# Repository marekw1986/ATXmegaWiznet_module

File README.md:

# ATXmegaWiznet_module

Flash
avrdude -p x128a3u -c avrispmkII -P usb -U flash:w:code.debug.elf

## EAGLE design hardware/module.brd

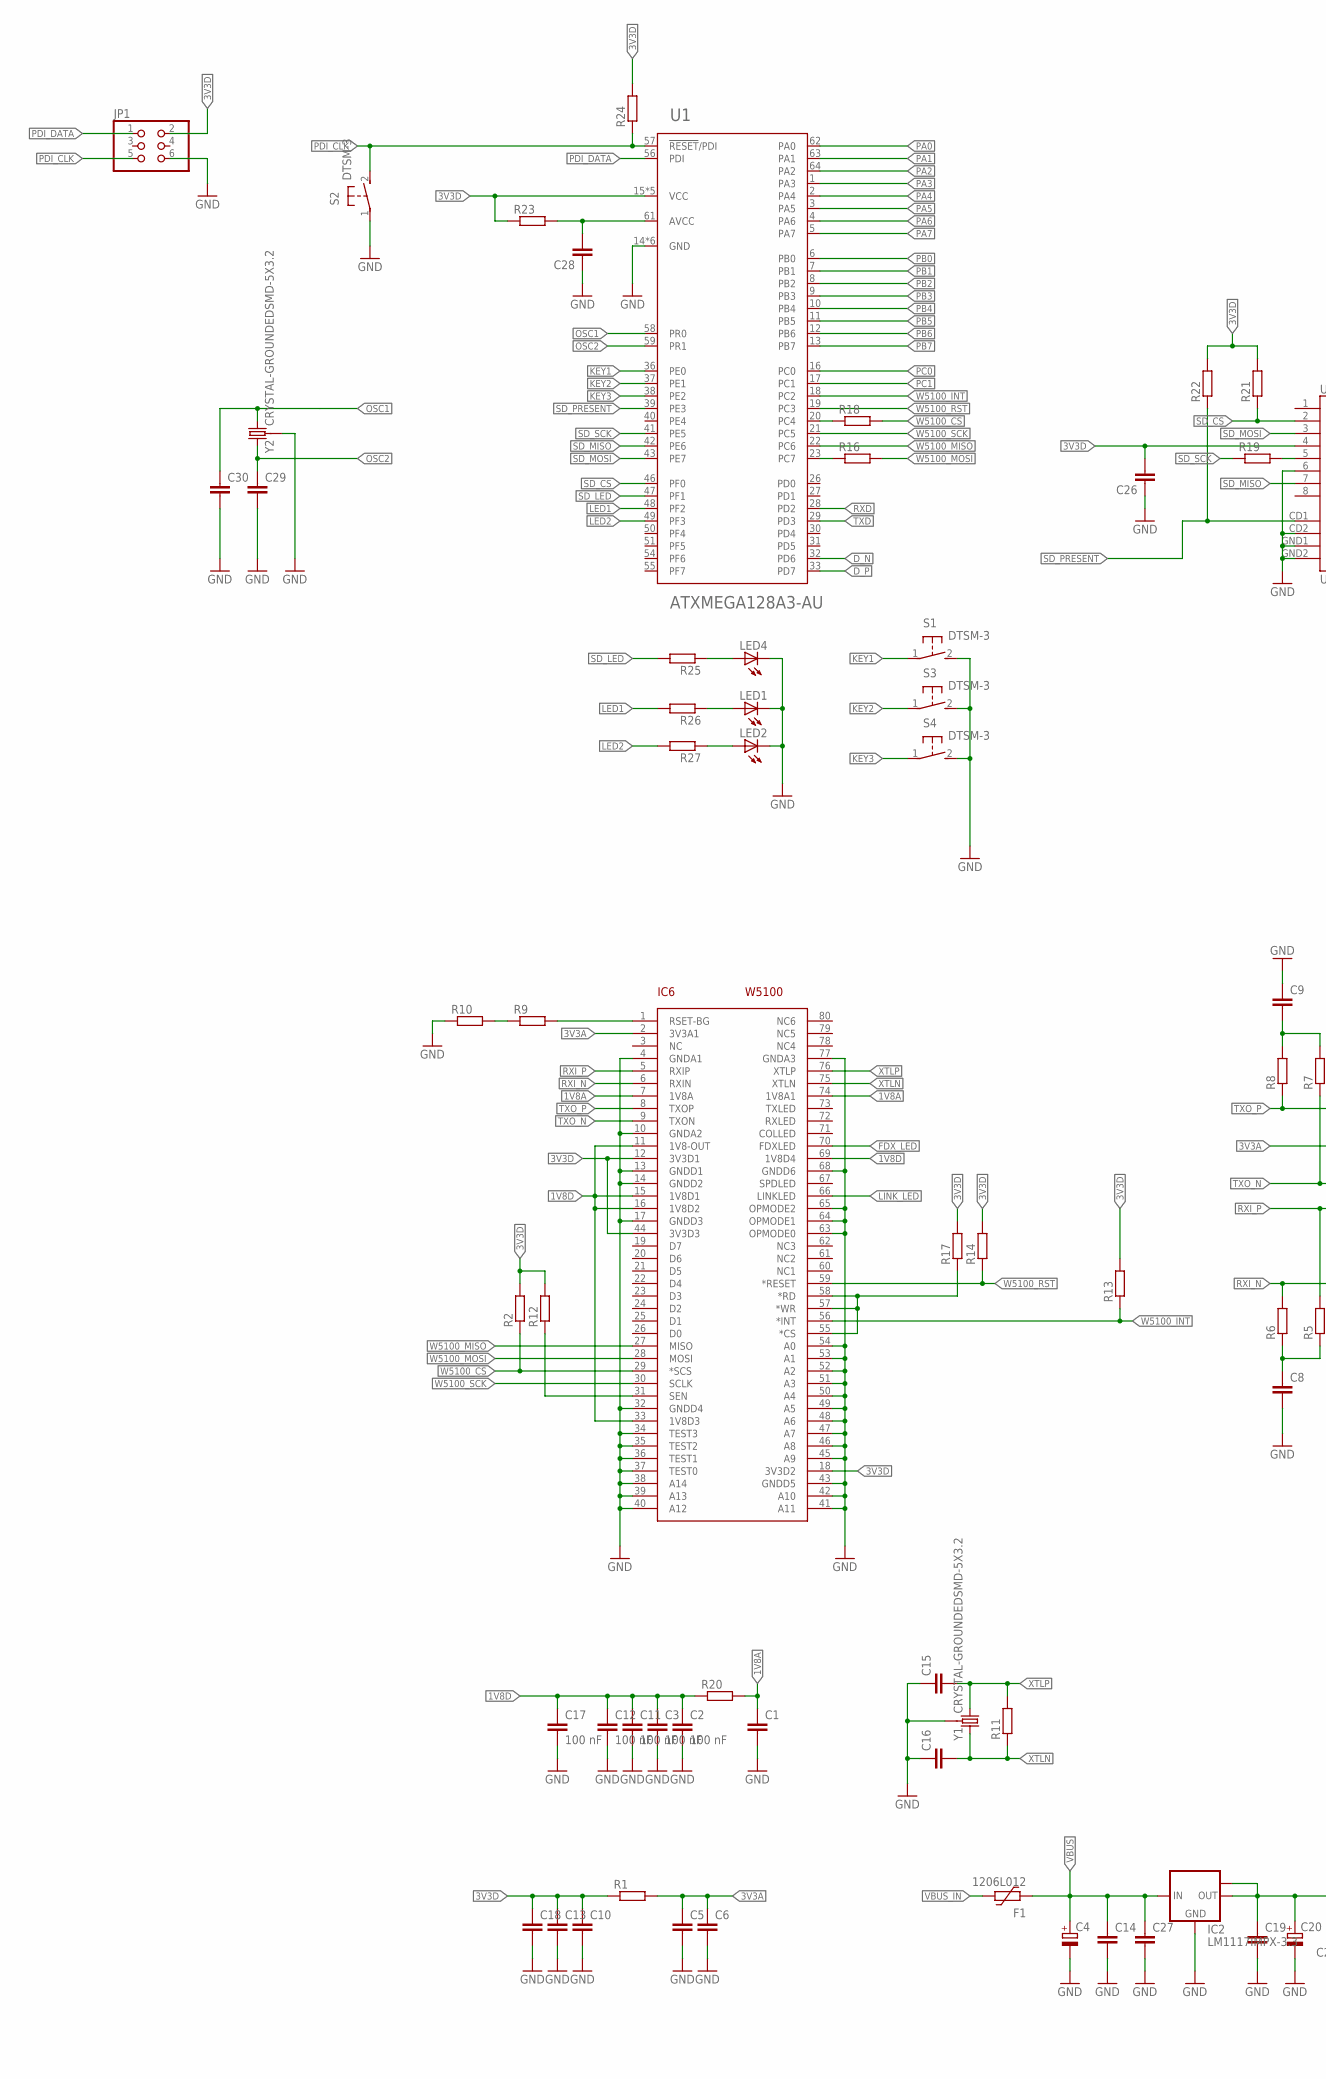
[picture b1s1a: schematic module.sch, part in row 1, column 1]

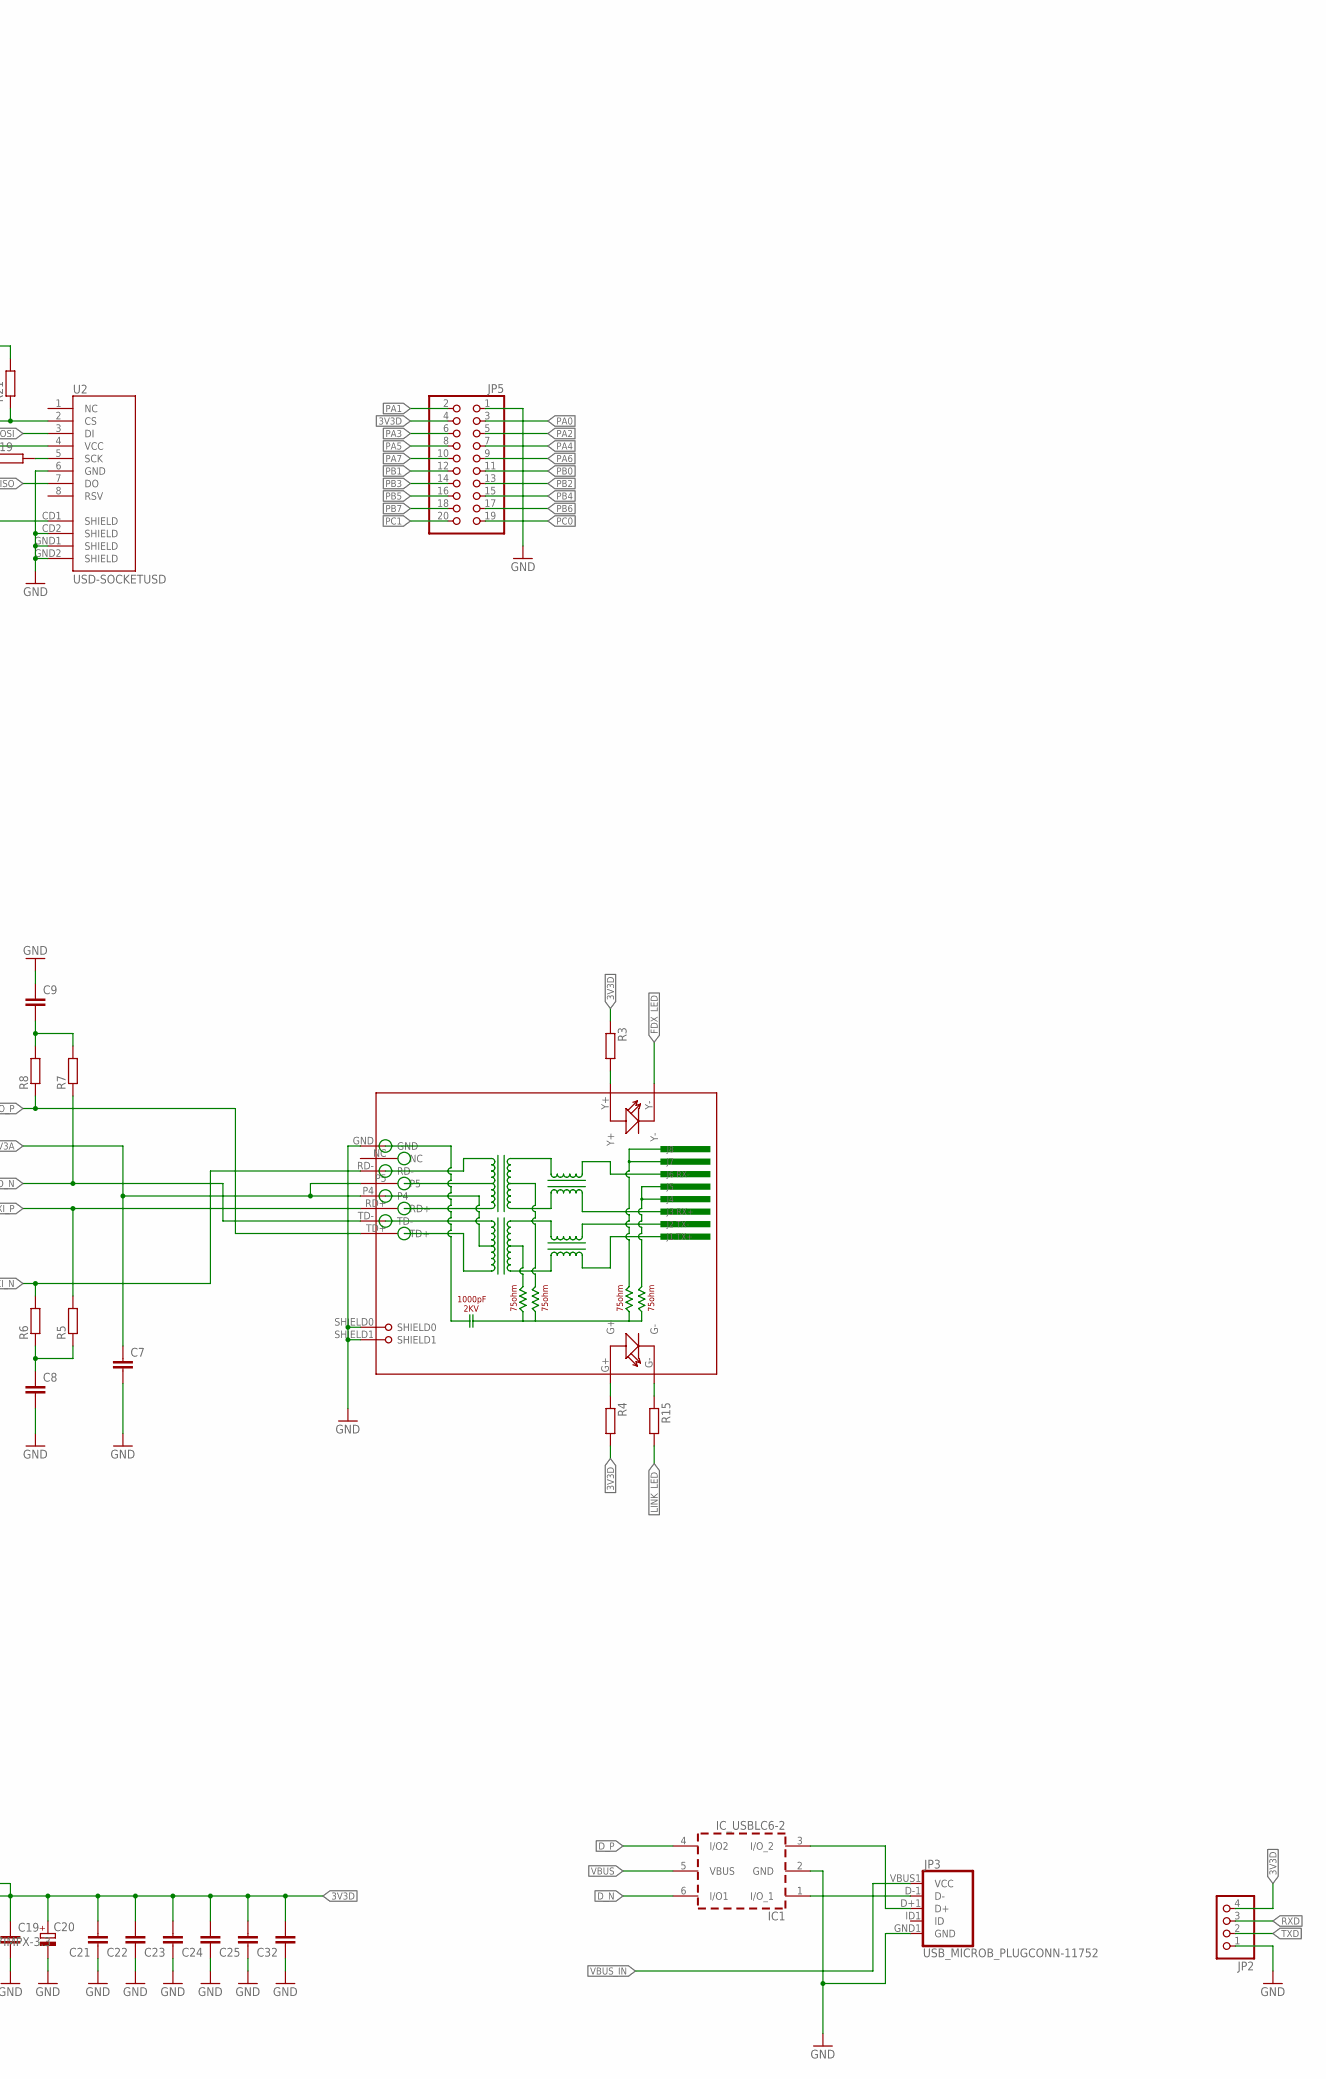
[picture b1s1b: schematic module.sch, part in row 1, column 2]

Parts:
C1, C5, C6, C7, C8, C9, C14, C15, C16, C19, C26, C27, C29, C30, C32: C-EUC0603; C0603
C2, C11, C12, C17: 100 nF; C0402
C3: 100 nF; C0603
C4, C20: CPOL-EUSMCB; SMC_B
C10, C13, C18, C21, C22, C23, C24, C25, C28: C-EUC0402; C0402
F1: 1206L012; 1206L
IC1: IC_USBLC6-2; SOT-23-6L
IC2: LM1117IMPX-3.3; SOT223
IC6: W5100; SQFP-S-10X10-80
JP1: PINHD-2X3; 2X03
JP2: PINHD-1X4; 1X04
JP3: USB_MICROB_PLUGCONN-11752; USB-B-MICRO-SMD_V03
JP5: PINHD-2X10_2.54-SMD; 2X10SMD
LED1, LED2, LED4: LEDCHIPLED_0805; CHIPLED_0805
R1, R20, R23: R-EU_R0805; R0805
R2, R3, R4, R5, R6, R7, R8, R9, R10, R11, R13, R15, R16, R17, R18, R19, R21, R22, R24, R25, R26, R27: R-EU_R0603; R0603
R12, R14: R-EU_R0402; R0402
RJ1: HR911105A
S1, S2, S3, S4: DTSM-3
U1: ATXMEGA128A3-AU; TQFP-64A-64
U2: USD-SOCKETUSD; USD-SOCKET-PP
Y1, Y2: CRYSTAL-GROUNDEDSMD-5X3.2; CRYSTAL-SMD-5X3.2-4PAD

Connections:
1V8A: C1.1, IC6.7 (1V8A), IC6.74 (1V8A1), R20.2
1V8D: C2.1, C3.1, C11.1, C12.1, C17.1, IC6.11 (1V8-OUT), IC6.15 (1V8D1), IC6.16 (1V8D2), IC6.33 (1V8D3), IC6.69 (1V8D4), R20.1
3V3A: C5.1, C6.1, C7.1, IC6.2 (3V3A1), R1.2, RJ1.P4, RJ1.P5
3V3D: C10.1, C13.1, C18.1, C19.1, C20.+, C21.2, C22.2, C23.2, C24.2, C25.2, C26.2, C32.2, IC2.2 (OUT), IC2.TAB (OUT1), IC6.12 (3V3D1), IC6.18 (3V3D2), IC6.44 (3V3D3), JP1.2, JP2.4, JP5.4, R1.1, R2.2, R3.1, R4.2, R12.2, R13.2, R14.2, R17.2, R21.2, R22.2, R23.1, R24.2, U1.15 (VCC), U1.25 (VCC), U1.35 (VCC), U1.45 (VCC), U1.53 (VCC), U2.4 (VCC)
AVCC: C28.2, R23.2, U1.61 (AVCC)
DN: IC1.3 (I/O_2), JP3.D+1 (D+)
DP: IC1.1 (I/O_1), JP3.D-1 (D-)
D_N: IC1.6 (I/O1), U1.32 (PD6)
D_P: IC1.4 (I/O2), U1.33 (PD7)
FDX_LED: IC6.70 (FDXLED), RJ1.Y-
GND: C1.2, C2.2, C3.2, C4.-, C5.2, C6.2, C7.2, C8.2, C9.1, C10.2, C11.2, C12.2, C13.2, C14.2, C15.1, C16.1, C17.2, C18.2, C19.2, C20.-, C21.1, C22.1, C23.1, C24.1, C25.1, C26.1, C27.2, C28.1, C29.2, C30.2, C32.1, IC1.2 (GND), IC2.1 (GND), IC6.4 (GNDA1), IC6.10 (GNDA2), IC6.13 (GNDD1), IC6.14 (GNDD2), IC6.17 (GNDD3), IC6.32 (GNDD4), IC6.34 (TEST3), IC6.35 (TEST2), IC6.36 (TEST1), IC6.37 (TEST0), IC6.38 (A14), IC6.39 (A13), IC6.40 (A12), IC6.41 (A11), IC6.42 (A10), IC6.43 (GNDD5), IC6.45 (A9), IC6.46 (A8), IC6.47 (A7), IC6.48 (A6), IC6.49 (A5), IC6.50 (A4), IC6.51 (A3), IC6.52 (A2), IC6.53 (A1), IC6.54 (A0), IC6.63 (OPMODE0), IC6.64 (OPMODE1), IC6.65 (OPMODE2), IC6.68 (GNDD6), IC6.77 (GNDA3), JP1.6, JP2.1, JP3.GND1 (GND), JP5.1, LED1.C, LED2.C, LED4.C, R10.1, RJ1.GND, RJ1.SHIELD0, RJ1.SHIELD1, S1.2, S2.1, S3.2, S4.2, U1.14 (GND), U1.24 (GND), U1.34 (GND), U1.44 (GND), U1.52 (GND), U1.60 (GND), U2.6 (GND), U2.CD2 (SHIELD), U2.GND1 (SHIELD), U2.GND2 (SHIELD), Y1.2 (3), Y1.4 (3), Y2.2 (3), Y2.4 (3)
KEY1: S1.1, U1.36 (PE0)
KEY2: S3.1, U1.37 (PE1)
KEY3: S4.1, U1.38 (PE2)
LED1: R26.2, U1.48 (PF2)
LED2: R27.2, U1.49 (PF3)
LINK_LED: IC6.66 (LINKLED), R15.2
unnamed: R4.1, RJ1.G+
unnamed: R3.2, RJ1.Y+
unnamed: C9.2, R7.2, R8.2
unnamed: C8.1, R5.1, R6.1
unnamed: R15.1, RJ1.G-
unnamed: IC6.1 (RSET-BG), R9.2
unnamed: R9.1, R10.2
unnamed: IC6.31 (SEN), R12.1
unnamed: R16.1, U1.23 (PC7)
unnamed: R19.2, U2.5 (SCK)
unnamed: LED4.A, R25.1
unnamed: LED1.A, R26.1
unnamed: LED2.A, R27.1
unnamed: IC6.55 (*CS), IC6.57 (*WR), IC6.58 (*RD), R17.1
OSC1: C30.1, U1.58 (PR0), Y2.1 (2)
OSC2: C29.1, U1.59 (PR1), Y2.3 (1)
PA0: JP5.3, U1.62 (PA0)
PA1: JP5.2, U1.63 (PA1)
PA2: JP5.5, U1.64 (PA2)
PA3: JP5.6, U1.1 (PA3)
PA4: JP5.7, U1.2 (PA4)
PA5: JP5.8, U1.3 (PA5)
PA6: JP5.9, U1.4 (PA6)
PA7: JP5.10, U1.5 (PA7)
PB0: JP5.11, U1.6 (PB0)
PB1: JP5.12, U1.7 (PB1)
PB2: JP5.13, U1.8 (PB2)
PB3: JP5.14, U1.9 (PB3)
PB4: JP5.15, U1.10 (PB4)
PB5: JP5.16, U1.11 (PB5)
PB6: JP5.17, U1.12 (PB6)
PB7: JP5.18, U1.13 (PB7)
PC0: JP5.19, U1.16 (PC0)
PC1: JP5.20, U1.17 (PC1)
PDI_CLK: JP1.5, R24.1, S2.2, U1.57 (!RESET!/PDI)
PDI_DATA: JP1.1, U1.56 (PDI)
RXD: JP2.3, U1.28 (PD2)
RXI_N: IC6.6 (RXIN), R6.2, RJ1.RD-
RXI_P: IC6.5 (RXIP), R5.2, RJ1.RD+
SD_CS: R21.1, U1.46 (PF0), U2.2 (CS)
SD_LED: R25.2, U1.47 (PF1)
SD_MISO: U1.42 (PE6), U2.7 (DO)
SD_MOSI: U1.43 (PE7), U2.3 (DI)
SD_PRESENT: R22.1, U1.39 (PE3), U2.CD1 (SHIELD)
SD_SCK: R19.1, U1.41 (PE5)
TXD: JP2.2, U1.29 (PD3)
TXO_N: IC6.9 (TXON), R7.1, RJ1.TD-
TXO_P: IC6.8 (TXOP), R8.1, RJ1.TD+
VBUS: C4.+, C14.1, C27.1, F1.2, IC1.5 (VBUS), IC2.3 (IN)
VBUS_IN: F1.1, JP3.VBUS1 (VCC)
W5100_CS: IC6.29 (*SCS), R2.1, R18.2
W5100_INT: IC6.56 (*INT), R13.1, U1.18 (PC2)
W5100_MISO: IC6.27 (MISO), U1.22 (PC6)
W5100_MOSI: IC6.28 (MOSI), R16.2
W5100_RST: IC6.59 (*RESET), R14.1, U1.19 (PC3)
W5100_SCK: IC6.30 (SCLK), U1.21 (PC5)
XTLN: C16.2, IC6.75 (XTLN), R11.1, Y1.3 (1)
XTLP: C15.2, IC6.76 (XTLP), R11.2, Y1.1 (2)
_W5100_CS: R18.1, U1.20 (PC4)

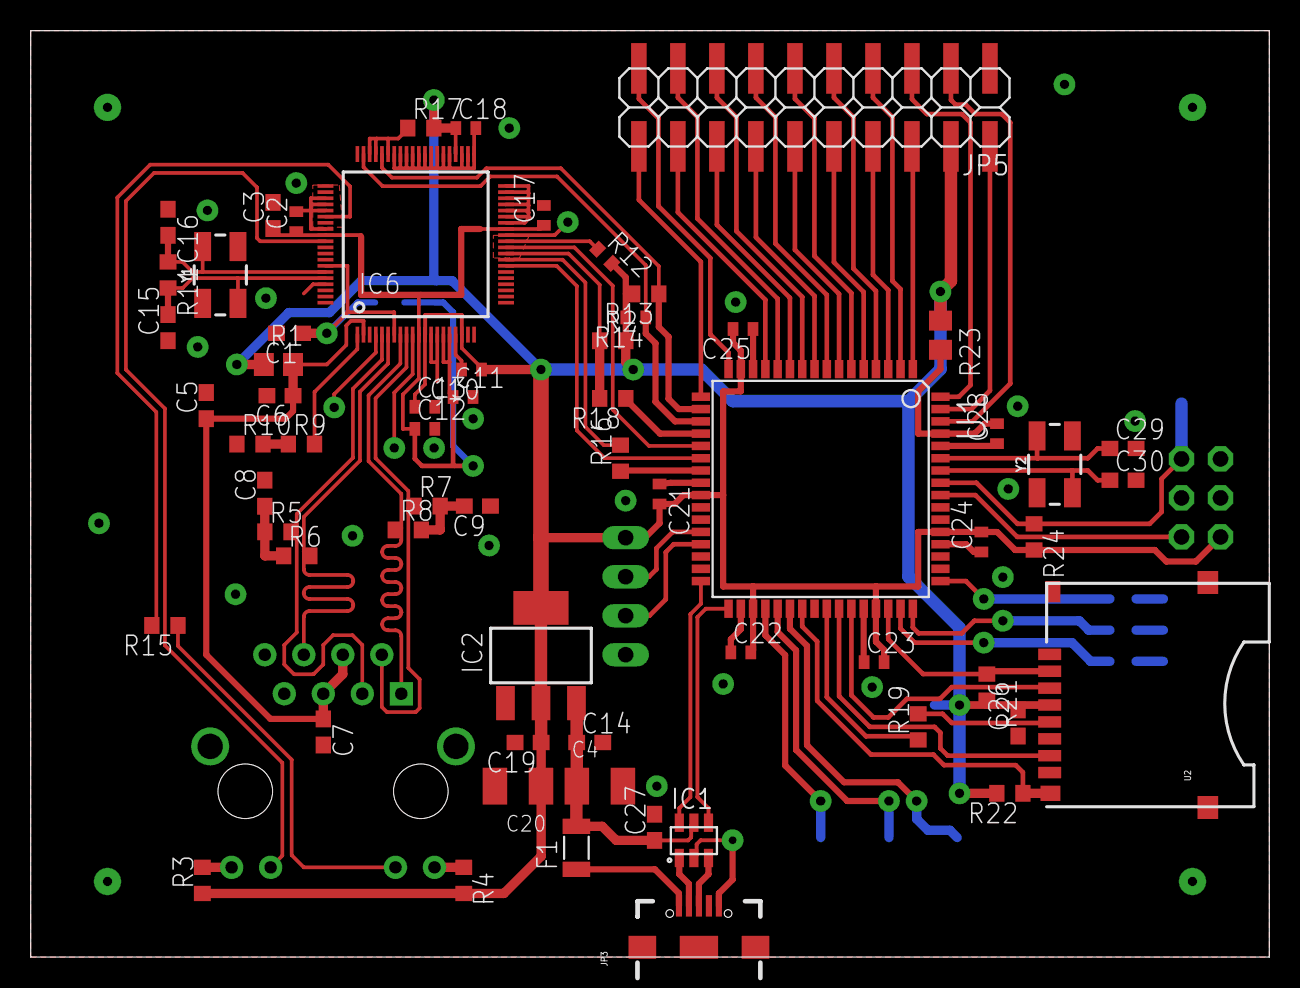
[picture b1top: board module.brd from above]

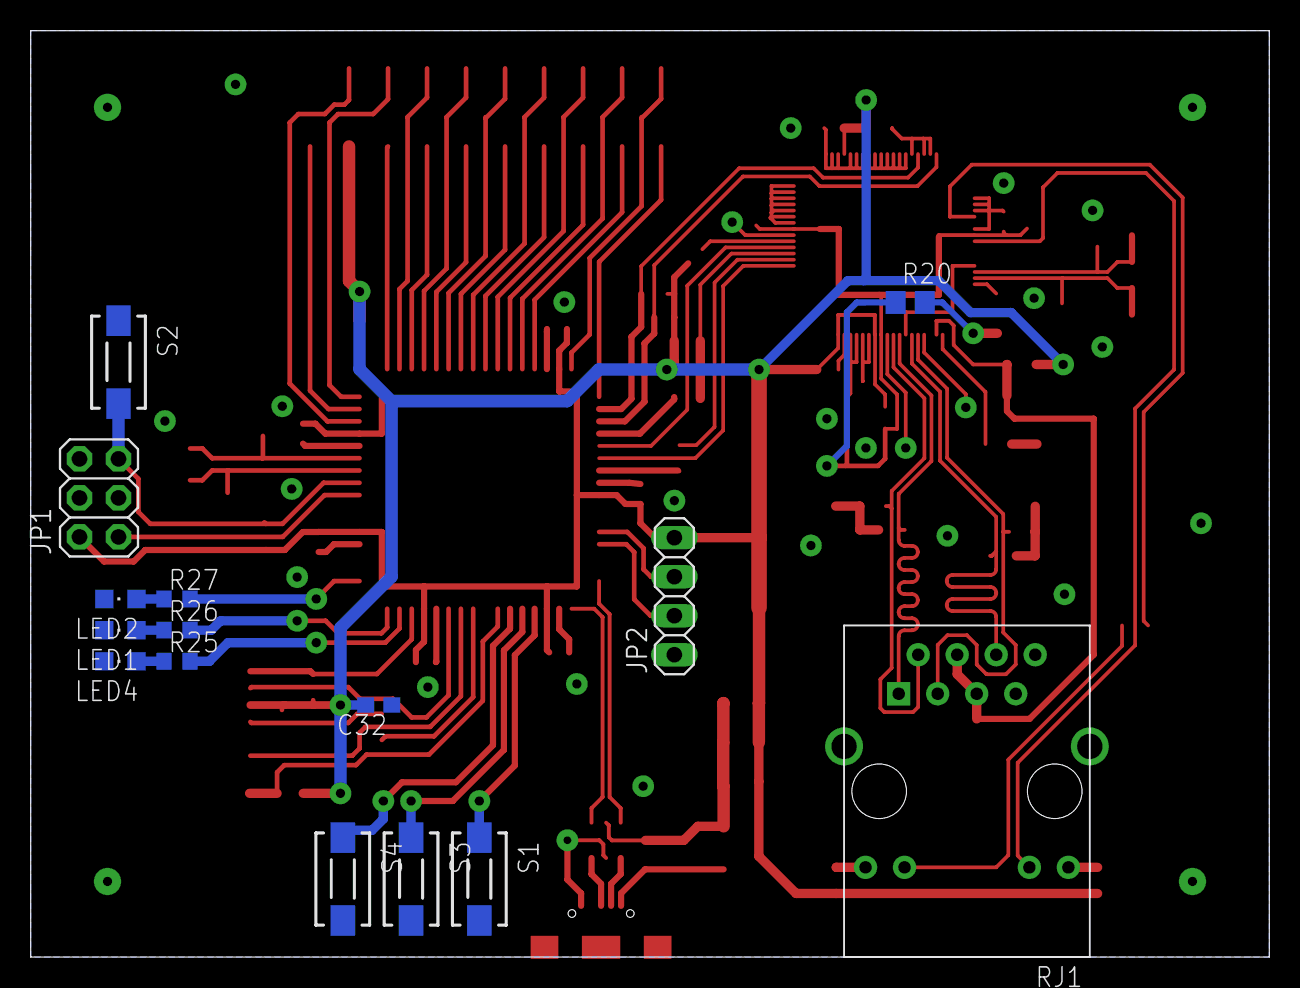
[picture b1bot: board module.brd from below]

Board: 2 copper layers, 80.6 x 60.3 mm, 78 parts (15 on the bottom side), 76 nets.

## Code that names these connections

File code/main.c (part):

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}

static inline void initialize_peripherals (void) {
    PORTF_DIRSET = PIN2_bm; //LED1
    PORTF_DIRSET = PIN3_bm; //LED2
    PORTD_DIRCLR = PIN2_bm; //PD2 is RX
    PORTD_DIRSET = PIN3_bm; //PD3 is TX
    PORTE_DIRCLR = PIN0_bm; //KEY 1 input
    PORTE_OUTSET = PIN0_bm; //KEY 1 pullup
    PORTE_DIRCLR = PIN1_bm; //KEY 2 input
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    PORTE_OUTSET = PIN2_bm; //KEY 3 pullup
    PORTE_DIRCLR = PIN3_bm; //SD PRESENT input
    PORTE_DIRSET = PIN4_bm; //PE4 is SPIE SS, should be an output to avoid issues.
    PORTE_DIRSET = PIN5_bm; //SD_SCK output
    PORTE_DIRCLR = PIN6_bm; //SD_MISO input
    PORTE_DIRSET = PIN7_bm; //SD_MOSI output
    PORTF_DIRSET = PIN0_bm; //SD_CS output
    PORTF_OUTSET = PIN0_bm; //SD_CS high
    PORTF_DIRSET = PIN1_bm; //SD_LED output
    PORTC_DIRCLR = PIN2_bm; //W5100_INT input
    PORTC_DIRSET = PIN3_bm; //W5100_RST output
    PORTC_OUTSET = PIN3_bm; //W5100_RST high
    PORTC_DIRSET = PIN4_bm; //W5100_CS output
    PORTC_OUTSET = PIN4_bm; //W5100_CS high
    PORTC_DIRSET = PIN5_bm; //W5100_SCK output
    PORTC_DIRCLR = PIN6_bm; //W5100_MISO input
    PORTC_DIRSET = PIN7_bm; //W5100_MOSI output
    
    //INITIALIZE SPI INTERFACES!
    
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
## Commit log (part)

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2020-09-21 Some changes
2020-11-09 cleaned
2021-03-12 gitignore
2025-10-19 Attempt to add Paho MQTT embedded library
2025-10-19 Paho MQTT Embedded library added
2025-10-19 MQTT example added to main.c
2025-10-19 MQTTServer excluded from current configuation
2025-10-19 Minor fix
2025-11-20 Add submodule wiznet ioLibrary_Driver
2025-11-27 Wizchip SPI driver
2025-11-27 Old network drivers and libraried removed
2025-11-27 Project updated
2025-11-27 Minor update
2025-11-29 MQTT added
2025-11-29 MQTT testing
2025-11-29 Include directory added to config to avoid meddling with original library paths
2025-11-30 SNTP update
2025-12-05 get_fattime implementation
2025-12-05 Checking PHY status at init excluded from compilation for W5100
2025-12-06 Flash command added to readme
2026-01-09 WolfMQTT added (work in progress)
2026-01-10 MQTTNet added
2026-01-10 mqttnet close added
2026-01-18 str to ip
2026-01-18 WolfMQTT related updates

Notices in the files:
parts and their libraries:
SparkFun-Clocks: Licensing: Creative Commons ShareAlike 4.0 International - https://creativecommons.org/licenses/by-sa/4.0
